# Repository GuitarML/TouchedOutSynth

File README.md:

# TouchedOut Sampler

The TouchedOut Polysynth is a polyphonic capacitive touch synth on a PCB, using the Daisy Seed. 
Two Adafruit MPR121 capacitive touch modules are used for keys and buttons. The firmware 
was designed and built using Arduino IDE with DaisyDuino. See Electrosmith's tutorials for
setting up the DaisyDuino environment with Arduino IDE. This repo also includes the
KiCad schematic and pcb files for ordering your own from a PCB manufacturer (JLCPcb gerbers provided).

[Video Demos on YouTube](https://youtu.be/tRJoIYXkm-U?si=PkRd3XZ30BAMkGUb)

## Microphone Circuit

The added microphone circuit for the TouchedOutSampler firmware is shown above. The mic used is from [Adafruit](https://www.adafruit.com/product/1063?srsltid=AfmBOooQ07_40sVdienoSQDztJte4-cMyLQY7wpDJVhW7ct12bVJHef1), MAX4466.
The 100uF capacitor on the audio line couples the audio to AC, as the output from the MAX4466 is DC coupled.
The RC filter using the 100 ohm resistior and 100uF capacitor was required for noise reduction. There 
is alot of noise coming from the Daisy Seed 3v3A power, but this RC filter does a good job of filtering it out. 

## Arduino IDE Setup

Follow this tutorial to set up DaisyDuino in Arduino IDE:
[How to Add Daisy Support to Arduino IDE](https://youtu.be/UyQWK8JFTps?si=kI6pP10nuPIkyu_V)

IMPORTANT!!! Updating Adafruit_MPR121 package to version 1.2.0 breaks functionality due to I2C incompatibilites. Use Adafruit_MPR121 version 1.1.3

Use these Tools settings in your Arduino IDE (pay attention to -O3 optimization and USB support: generic serial supercede USART)

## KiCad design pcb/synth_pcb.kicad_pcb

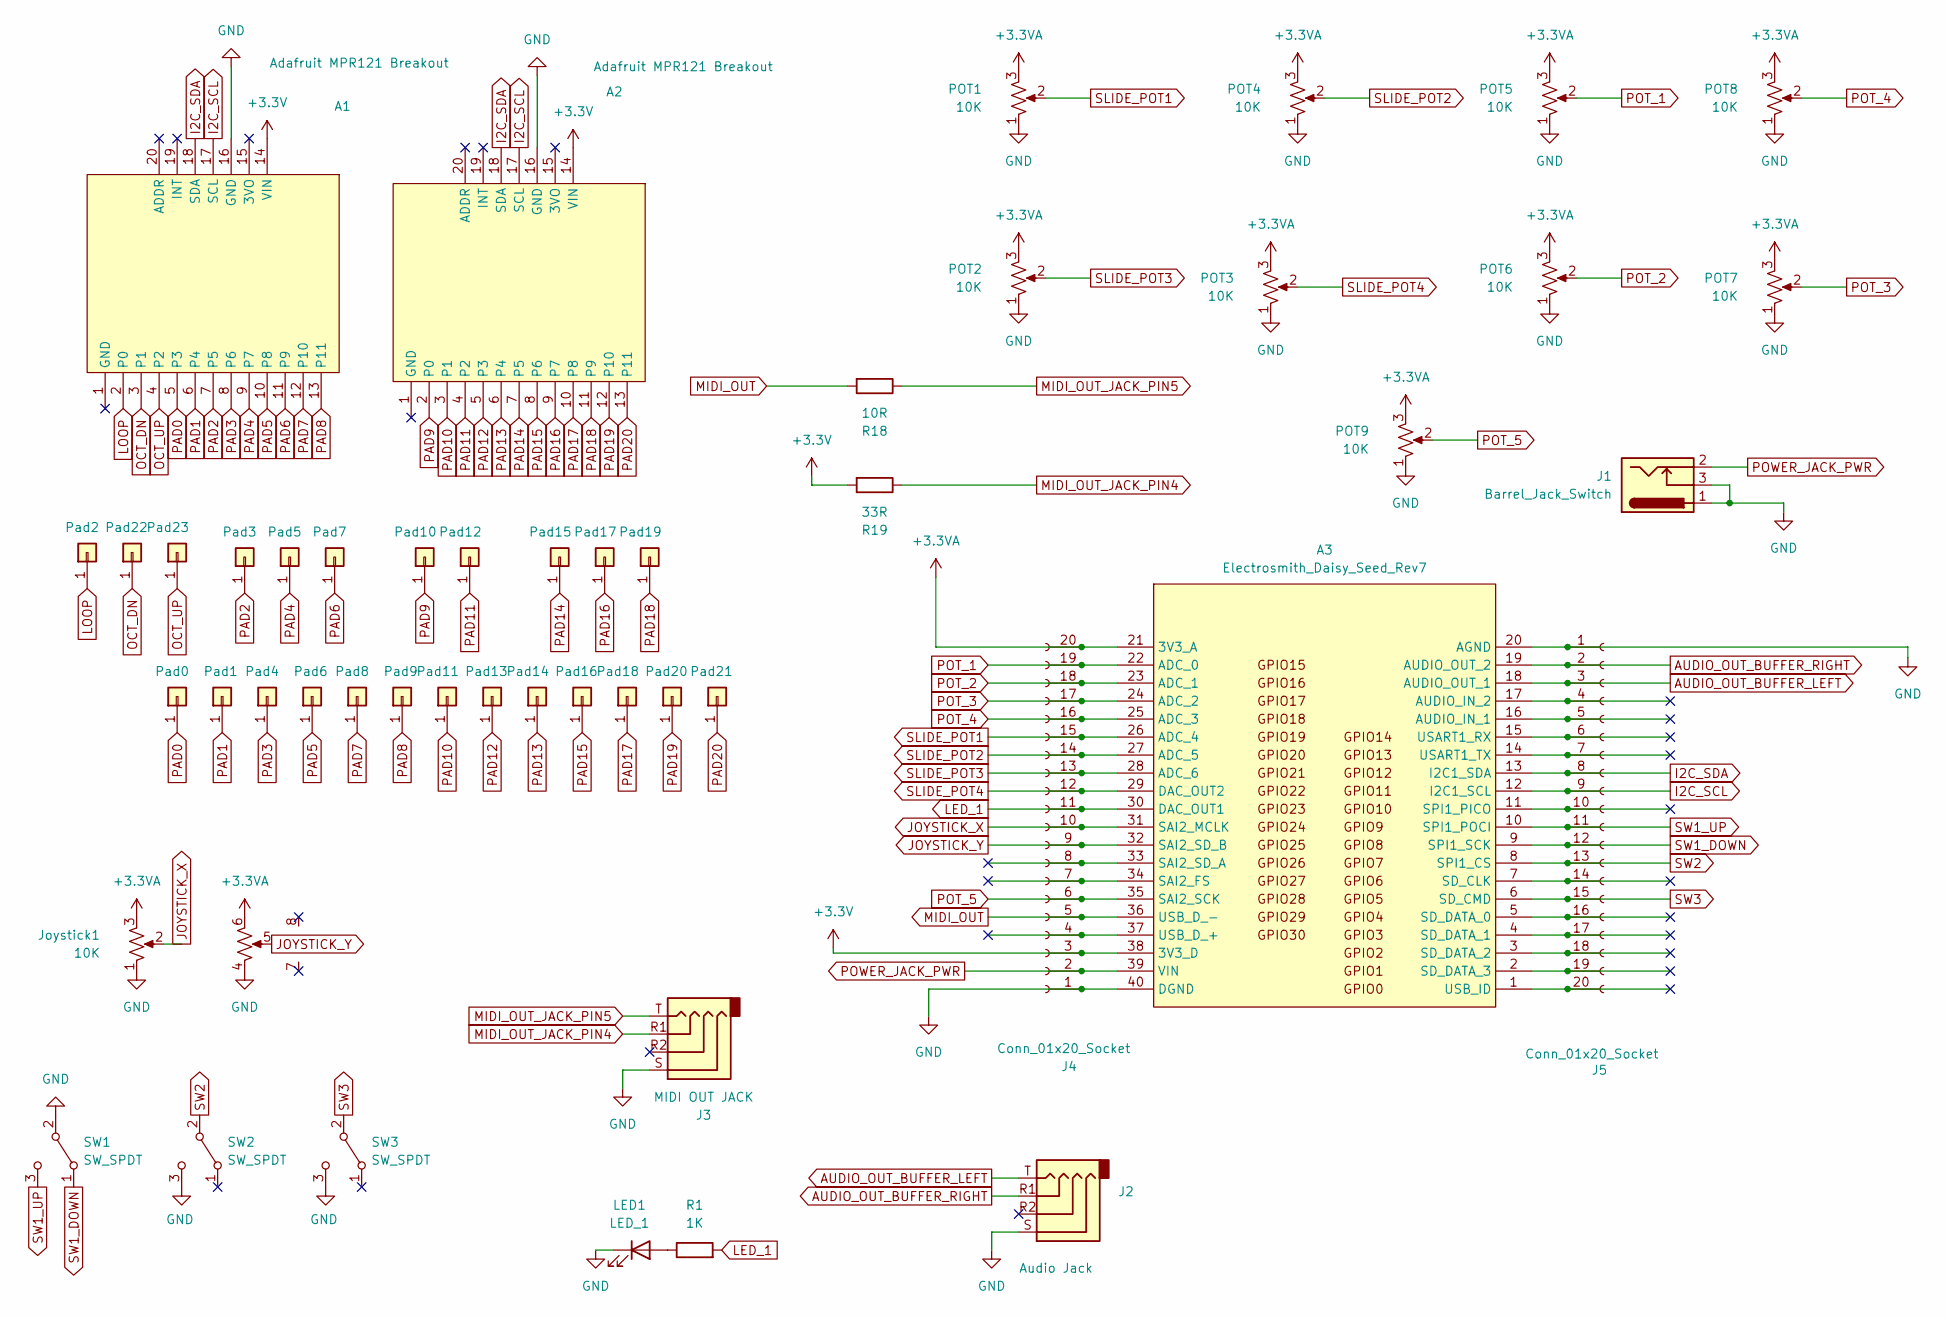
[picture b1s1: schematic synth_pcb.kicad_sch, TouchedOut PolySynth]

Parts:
A1, A2: Adafruit MPR121 Breakout; Adafruit_MPR121
A3: Electrosmith_Daisy_Seed_Rev7
J1: Barrel_Jack_Switch; Generic_PowerJack
J2: Audio Jack; Audio_TRRS-PJ-320A
J3: MIDI OUT JACK; Audio_TRRS-PJ-320A
J4, J5: Conn_01x20_Socket; PinSocket1x20_P2.54mm_Vertical_JLCPCB
Joystick1: 10K; Adafruit_2ax_joystick
LED1: LED_1; PinHeader_1x02_P2.54mm_Vertical
POT1, POT2, POT3, POT4: 10K; Slide_Potentiometer_35mm
POT5, POT6, POT7, POT8, POT9: 10K; Potentiometer_Bourns_PRS11R
Pad0, Pad1, Pad2, Pad3, Pad4, Pad5, Pad6, Pad7, Pad8, Pad9, Pad10, Pad11, Pad12, Pad13, Pad14, Pad15, Pad16, Pad17, Pad18, Pad19, Pad20, Pad21, Pad22, Pad23: TestPoint_THTPad_D2.0mm_Drill1.0mm
R1: 1K; R_Axial_DIN0207_L6.3mm_D2.5mm_P7.62mm_Horizontal
R18: 10R; R_Axial_DIN0207_L6.3mm_D2.5mm_P7.62mm_Horizontal
R19: 33R; R_Axial_DIN0207_L6.3mm_D2.5mm_P7.62mm_Horizontal
SW1, SW2, SW3: SW_SPDT; SW_Toggle_SPDT_lugs

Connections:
+3.3V: A1.14 (VIN), A2.14 (VIN), A3.38 (3V3_D), J4.3, R19.2
+3.3VA: A3.21 (3V3_A), J4.20, Joystick1.3, Joystick1.6, POT1.3, POT2.3, POT3.3, POT4.3, POT5.3, POT6.3, POT7.3, POT8.3, POT9.3
AUDIO_OUT_BUFFER_LEFT: A3.18 (AUDIO_OUT_1), J2.T, J5.3, J5.T
AUDIO_OUT_BUFFER_RIGHT: A3.19 (AUDIO_OUT_2), J2.R1, J5.2, J5.R1
GND: A1.16 (GND), A2.16 (GND), A3.20 (AGND), A3.40 (DGND), J1.1, J1.3, J2.S, J3.S, J4.1, J5.1, J5.S, Joystick1.1, Joystick1.4, LED1.1 (K), POT1.1, POT2.1, POT3.1, POT4.1, POT5.1, POT6.1, POT7.1, POT8.1, POT9.1, SW1.2 (B), SW2.3 (C), SW3.3 (C)
I2C_SCL: A1.17 (SCL), A2.17 (SCL), A3.12 (I2C1_SCL), J5.9
I2C_SDA: A1.18 (SDA), A2.18 (SDA), A3.13 (I2C1_SDA), J5.8
JOYSTICK_X: A3.31 (SAI2_MCLK), J4.10, Joystick1.2
JOYSTICK_Y: A3.32 (SAI2_SD_B), J4.9, Joystick1.5
LED_1: J4.11, R1.2
LOOP: A1.2 (P0), Pad2.1
MIDI_OUT: A3.36 (USB_D_-), J4.5, R18.2
MIDI_OUT_JACK_PIN4: J3.R1, R19.1
MIDI_OUT_JACK_PIN5: J3.T, R18.1
unnamed: A3.1 (USB_ID), J5.20
unnamed: A3.2 (SD_DATA_3), J5.19
unnamed: A3.3 (SD_DATA_2), J5.18
unnamed: A3.4 (SD_DATA_1), J5.17
unnamed: A3.5 (SD_DATA_0), J5.16
unnamed: A3.7 (SD_CLK), J5.14
unnamed: A3.11 (SPI1_PICO), J5.10
unnamed: A3.14 (USART1_TX), J5.7
unnamed: A3.15 (USART1_RX), J5.6
unnamed: A3.16 (AUDIO_IN_1), J5.5
unnamed: A3.17 (AUDIO_IN_2), J5.4
unnamed: A3.33 (SAI2_SD_A), J4.8
unnamed: A3.34 (SAI2_FS), J4.7
unnamed: A3.37 (USB_D_+), J4.4
unnamed: LED1.2 (A), R1.1
OCT_DN: A1.3 (P1), Pad22.1
OCT_UP: A1.4 (P2), Pad23.1
PAD0: A1.5 (P3), Pad0.1
PAD1: A1.6 (P4), Pad1.1
PAD2: A1.7 (P5), Pad3.1
PAD3: A1.8 (P6), Pad4.1
PAD4: A1.9 (P7), Pad5.1
PAD5: A1.10 (P8), Pad6.1
PAD6: A1.11 (P9), Pad7.1
PAD7: A1.12 (P10), Pad8.1
PAD8: A1.13 (P11), Pad9.1
PAD9: A2.2 (P0), Pad10.1
PAD10: A2.3 (P1), Pad11.1
PAD11: A2.4 (P2), Pad12.1
PAD12: A2.5 (P3), Pad13.1
PAD13: A2.6 (P4), Pad14.1
PAD14: A2.7 (P5), Pad15.1
PAD15: A2.8 (P6), Pad16.1
PAD16: A2.9 (P7), Pad17.1
PAD17: A2.10 (P8), Pad18.1
PAD18: A2.11 (P9), Pad19.1
PAD19: A2.12 (P10), Pad20.1
PAD20: A2.13 (P11), Pad21.1
POT_1: A3.22 (ADC_0), J4.19, POT5.2
POT_2: A3.23 (ADC_1), J4.18, POT6.2
POT_3: A3.24 (ADC_2), J4.17, POT7.2
POT_4: A3.25 (ADC_3), J4.16, POT8.2
POT_5: A3.35 (SAI2_SCK), J4.6, POT9.2
POWER_JACK_PWR: A3.39 (VIN), J1.2, J4.2
SLIDE_POT1: A3.26 (ADC_4), J4.15, POT1.2
SLIDE_POT2: A3.27 (ADC_5), J4.14, POT4.2
SLIDE_POT3: A3.28 (ADC_6), J4.13, POT2.2
SLIDE_POT4: A3.29 (DAC_OUT2), J4.12, POT3.2
SW1_DOWN: A3.9 (SPI1_SCK), J5.12, SW1.1 (A)
SW1_UP: A3.10 (SPI1_POCI), J5.11, SW1.3 (C)
SW2: A3.8 (SPI1_CS), J5.13, SW2.2 (B)
SW3: A3.6 (SD_CMD), J5.15, SW3.2 (B)

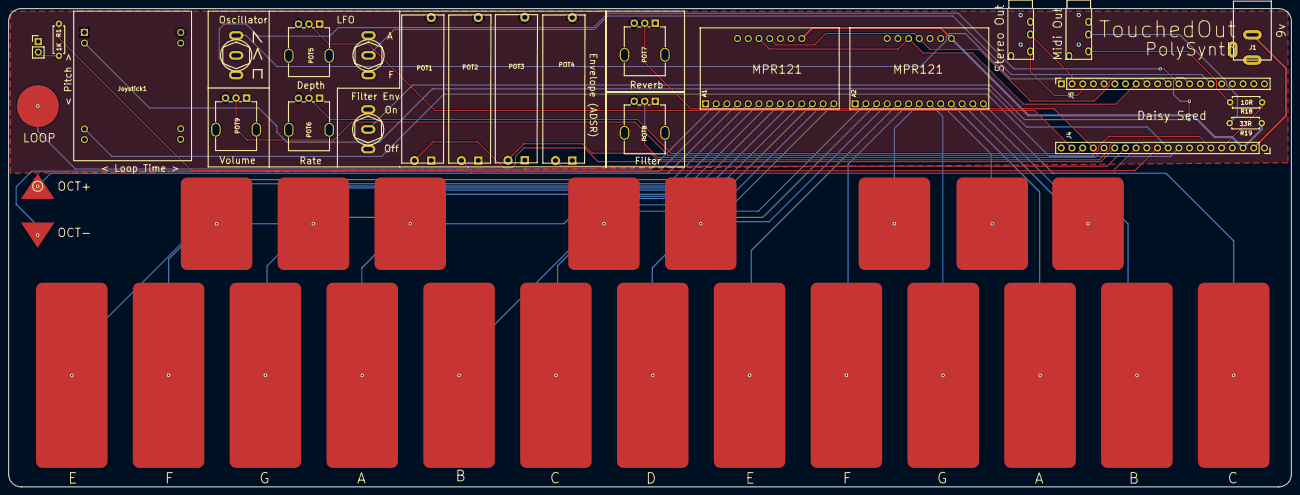
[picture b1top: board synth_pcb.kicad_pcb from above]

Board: 2 copper layers, 304.7 x 113.6 mm, 48 parts (0 on the bottom side), 52 nets.

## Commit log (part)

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2025-11-22 Fixed image link
2026-01-25 Updates for initial release
